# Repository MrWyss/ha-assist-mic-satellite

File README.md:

# Voice Assistant Mic Satellite

***<p align="center" style="text-align: center;">«The VA Mic Satellite is a compact, ESPHome-based microphone solution designed to integrate with your existing sound setup..»</p>***

## Changes

>📢 2025-11-23: Firmware release [v2.0.1](https://github.com/MrWyss/ha-assist-mic-satellite/releases/tag/v2.0.1) 
>
>Memory improvements: 
>
> - Allows to run 2 wake words simultaneously
> - ESPHome 2025.11.0
> 
>📢 2025-10-03: Firmware release [v2.0.0](https://github.com/MrWyss/ha-assist-mic-satellite/releases/tag/v2.0.0) 🎉🎉🎉: **Mayor Release**, this pushes the [M5Stack AtomS3](https://docs.m5stack.com/en/core/AtomS3) to **it's limit**. With these new features 
> - Option to change from "Okey Nabu" to "Hey Jarvis" and back
> - "Set Up Voice Assistant" wizard will run on first boot
> - ESPHome 2025.9.2
>
>... [Read more](https://github.com/MrWyss/ha-assist-mic-satellite/releases)
>
>📢 2024-08-19: Version 1 released. 🎉🎉🎉 and  [PCB rev. 3](https://github.com/MrWyss/ha-assist-mic-satellite/discussions/15#discussion-7049397) has arrived and tested successfully. 🥳. See the new firmware [in action](https://github.com/MrWyss/ha-assist-mic-satellite/discussions/16#discussioncomment-10387199) on a [mic stand](https://github.com/MrWyss/ha-assist-mic-satellite/discussions/16#discussioncomment-10387101) 😆.
>
>📢 2024-08-12: I just came across the [announcement](https://www.youtube.com/watch?v=Vp5q4RIwCX4) of **Satellite1** by [Future Proof Homes](https://futureproofhomes.net). It’s an amazing initiative! 😎 My project is entirely different and not comparable to theirs. The similar name is just a coincidence. Definitely check them out!

## Features

A ~~tiny~~ Atom version of the [ESP32-S3-BOX](https://esphome.io/projects/index.html)

- Local / On Device **wake word detection** (😲 holy cow, this works fast and so well)
- Redirect TTS to a configurable **media player entity** e.g. SONOS, to play the response
- HA **Assist Pipeline integration**
- Toggle **mute**, toggle **conversation text** and control display **brightness**
- **Show current state** (listening, idle, request, response) on the display. It is fairly readable, though it requires good eyesight 👀.
- **Timers** support (plural), realistically up to 4 timers
- Easy firmware flashing via the [web installer](https://mrwyss.github.io/ha-assist-mic-satellite/)
- Managed updates

### Roadmap

If anyone is interested in contributing, here are some ideas:

- [ ] Better alarm **sound files** [#10](https://github.com/MrWyss/ha-assist-mic-satellite/issues/10)
  
## TL;DR

Gather the following items: [M5Stack AtomS3](#bom), [pcb](#pcb), [pin headers and pin sockets](#bom) and an [INMP441](#bom) breakout board.
3D print the [case](#case), [assemble](#assembly) it, [flash the firmware](#firmware), [configure](#home-assistant) the device in Home Assistant.

## Try it out / Tricks

- **Wake Word**: "Okay Nabu" (or "Hey Jarvis")
- Create a timer, *Create a 3 minute timer for Bananas*, *Cancel Bananas timer*
- The display itself is also a button, so you can **long press (~800ms) to mute** the device, it stops listening for the wake word. Holding for ~10s factory resets the device.
- If you have [Music Assistant](https://music-assistant.io) you can change the **announcement volumes**. Goto the Music Assistant Addon -> Settings -> Players -> Your Speaker -> Configure -> Announcements configuration

## Hardware

### BOM

- [M5Stack AtomS3](https://docs.m5stack.com/en/core/AtomS3) ~15$
- [PCB](#pcb) ~5$ + shipping
- [Case](#case) ~0.5$ filament
- **INMP441** breakout board (usually comes with pin sockets) ~2$
  - 2x Pin socket 1x03 2.54mm (J3, J4)
- 1x Pin header 1x05 2.54mm (J1)
- 1x Pin header 1x04 2.54mm (J2)
- M2 x 5mm screw nylon or with metal with nylon washer (optional)

### PCB

The pcb was designed in KiCAD. [KiCAD Canvas Online View](https://kicanvas.org/?github=https%3A%2F%2Fgithub.com%2FMrWyss%2Fha-assist-mic-satellite%2Ftree%2Fmain%2Fpcb%2FMic%2520HAT%2520for%2520M5Stack%2520Atom) | [KiCad Project](pcb/Mic%20HAT%20for%20M5Stack%20Atom) | [PCB Step File](<pcb/Mic HAT for M5Stack Atom/Mic HAT for M5Stack Atom.step>)

Order from [PCBWay Project Link](https://www.pcbway.com/project/shareproject/HA_Assist_Mic_Satellite_f5cc4682.html) (🛒 affiliated link)

| PCB front | PCB back |
|:-------------------------:|:-------------------------:|
| | |

### Case

#### Hat

The case was designed in Fusion 360 and exported as 3mf files and step files. [Step files](case/step) | [3mf files](case/3mf)
It shouldn't need any supports for 3d printing, but I recommend printing it with your high detail settings. It is rather small.

- [Hat case body](case/3mf/MicHatCaseBody.3mf)
- [Hat case top](case/3mf/MicHatCaseTop.3mf)

#### Optional (boom, wind screen, stand)

[Boom for Grove connector](case/3mf/MicHatHolderGrove.3mf), the boom was designed for the Grove connector, as it is more centered. I sacrificed a sleeved USB cable and attached a Grove connector to it. It's supposed to be a press fit. [Mic wind screen](case/3mf/MicHatCaseWindShield.3mf), this is purely cosmetic and serves no functional purpose. [Mic stand](case/3mf/MicStandMicAll.3mf), to assemble the mic stand, you need a 8mm (~1 meter / hollow) aluminum rod. Cut into approximately three 10cm pieces, one 20cm (vertical) and one 25cm (horizontal).

### Assembly

Pretty straight forward. Solder the header sockets and pins to the pcb and to the INMP441.

>❗Check the direction of the header sockets and pins. Especially on the INMP441, the side with mic icon should face the same direction as the screen.

Put it in the case, screw it together and attach the HAT to the AtomS3.

## Software

- [Home Assistant](https://www.home-assistant.io) (*ESPHome not required only if you want to adopt the device*)
- [Music Assistant](https://music-assistant.io) (optional)
- A **media player entity** (e.g. media_player.office)

### Firmware

The firmware is available here: [Web Installer](https://mrwyss.github.io/ha-assist-mic-satellite/) or [ESPHome yaml](code/esphome/va-mic-sat-atoms3.yaml)

This has been frankensteined together from various sources. I will try to give [credit](#credits) where [credit](#credits) is due.

### Home Assistant

The device should get auto discovered.

We need to tick **Allow the device to perform Home Assistant actions**. Since the firmware will call the `media_player.play_media` service, we need to allow this.

While you here, click on **device** and change paste your media player entity id where the announcement should be played.

### Sounds

There are **two** sound files required. One for when the device is listening, this is the silent wav file, the second is for the alarm ringtone.

Currently the firmware is configured that the media player streams the files directly from github, in other words it (media_player) requires an internet connection. If you want to change this, adopt the device in ESPHome and change the following lines to something like this:

```yaml
substitutions:
  # ....
  timer_sound_file: media-source://media_source/local/my-alarm.mp3
  silence_sound_file: media-source://media_source/local/my-silence.mp3
```

To copy the sound files to for instance the home assistant, you can use the vscode addon or samba share. See more [Home Assistant Docs](https://www.home-assistant.io/integrations/media_source/)

## How it works

### Simplified Process

```mermaid
sequenceDiagram
    participant Mic Satellite
    participant Assist Pipeline
    participant media_player
    Mic Satellite->Mic Satellite: wake word detection
    Mic Satellite->>media_player: trigger action media_player.play_media (announcement / silent audio)
    media_player->media_player: lower volume
    Mic Satellite->Mic Satellite: listening  
    Mic Satellite->>Assist Pipeline: send intent audio
    Assist Pipeline->>Mic Satellite: response mp3_url
    Mic Satellite->>media_player: trigger action media_player.play_media (announcement / mp3_url)
    media_player->media_player: play response
```

### Wiring / Schematics

[KiCAD Schematic](<pcb/Mic HAT for M5Stack Atom/Mic HAT for M5Stack Atom.kicad_sch>) | [KiCAD Canvas Online View](https://kicanvas.org/?github=https%3A%2F%2Fgithub.com%2FMrWyss%2Fha-assist-mic-satellite%2Ftree%2Fmain%2Fpcb%2FMic%2520HAT%2520for%2520M5Stack%2520Atom)

All the the pcb hat does is connecting the INMP441 pins to the AtomS3 pins.

<details><summary>Pin mapping table</summary>

|AtomS3 Pin|INMP441 Pin|
|:----------:|:-----------:|
|3V3| VDD|
|GND | GND + L/R|
|G5 (GPIO5) | WS|
|G6 (GPIO6) | SCK|
|G7 (GPIO7) | SD|

</details>

Additionally, it exposes the remaining pins of the AtomS3 and adds two solder bridges (JP1 and JP2). G8, G38, and G39 are available to use for other purposes. So is the Grove connector (G1, G2). Power (+3V3 and +5V) and ground are also available.

The solder bridges are used to change the audio channel, left or right. There are two configurations:

- Left channel: JP1 bridged and JP2 not bridged (default)
- Right channel: JP1 not bridged and JP2 bridged

>❗To change the configuration, both solder bridges need to be modified. Cut one and bridge the other. I cloud otherwise short +3V3 to GND.

## Picture Gallery

<details><summary>Videos and Pictures</summary>

### Demo Video v1.0.0

https://github.com/user-attachments/assets/9a9f7f58-b787-4129-acef-4c1b4aa1fa7d

### Demo Pictures v1.0.0

### Close Ups

|Close up | Full device with cable&nbsp;&nbsp;&nbsp;&nbsp;&nbsp;&nbsp;&nbsp;&nbsp;&nbsp;&nbsp;&nbsp;&nbsp;&nbsp;&nbsp;&nbsp;&nbsp;&nbsp;&nbsp;&nbsp;&nbsp;&nbsp;&nbsp;&nbsp;&nbsp;&nbsp;&nbsp;&nbsp;&nbsp;&nbsp;&nbsp;&nbsp;&nbsp;&nbsp;&nbsp;&nbsp;&nbsp;&nbsp;&nbsp;&nbsp;&nbsp;&nbsp;&nbsp;&nbsp;&nbsp;&nbsp;&nbsp;&nbsp;&nbsp;&nbsp;&nbsp;&nbsp;&nbsp;&nbsp;&nbsp;&nbsp;&nbsp;|
|:-------------------------:|:-------------------------:|
| | |

### Archive

|Muted            |  Intent in Action|
|:-------------------------:|:-------------------------:|
| | |

</details>

## Background

I am not an electrical engineer nor a software developer. This project is for fun and to learn new things, such as PCB design with KiCad, CAD, and ready-made ESPHome projects.

I am aware that Nabu Casa is working on a [Voice Kit](https://github.com/esphome/voice-kit); in fact, many things are directly taken from their project.
I am excited to see what the final product will look like and might even buy it myself.

My motivation was to have a small device that integrates with my existing sound setup (SONOS, in my case) rather than having a separate speaker.

## License

I wasn't sure if I should use the same license as the ESPHome project, but I think it is fine.

## Contributing

**Please do**, create issues, pull requests, open a discussion or DM me here. I am happy to help and learn from you.

## Credits

- [HA Voice Kit](https://github.com/esphome/voice-kit)
- [ESPHome Voice Assistant Github Repo](https://github.com/esphome/firmware/tree/main/voice-assistant/)
- [Smart Home Circle](https://smarthomecircle.com/How-I-created-my-voice-assistant-with-on-device-wake-word-using-home-assistant)
- [Community](https://community.home-assistant.io/t/esphome-voice-assistant-speech-output-to-home-assistant-media-player/588337/18)
- And obviously the Nabu Casa team

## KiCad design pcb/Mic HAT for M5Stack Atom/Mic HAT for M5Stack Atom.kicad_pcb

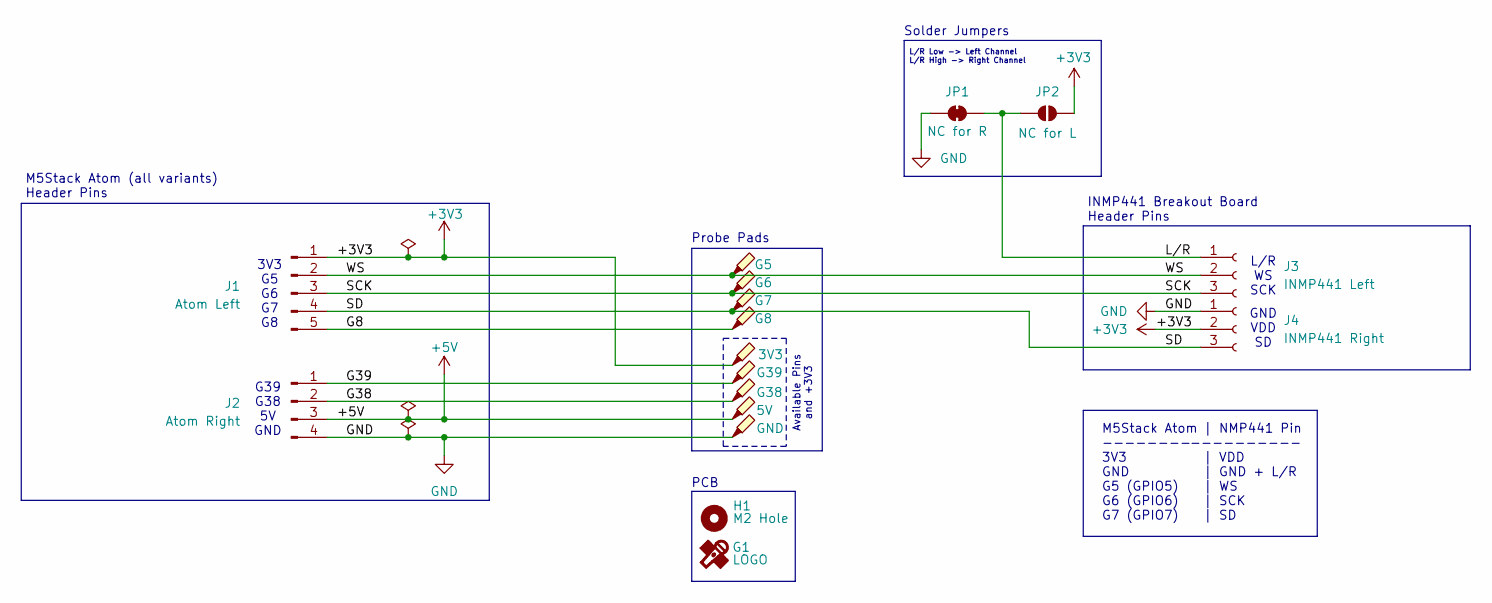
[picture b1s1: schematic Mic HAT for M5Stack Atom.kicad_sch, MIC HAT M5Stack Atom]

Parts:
3V3: 3V3; TestPoint_THTPad_D1.5mm_Drill0.7mm
5V1: 5V; TestPoint_THTPad_D1.5mm_Drill0.7mm
G1: LOGO; Logo
G5: G5; TestPoint_THTPad_D1.5mm_Drill0.7mm
G6: G6; TestPoint_THTPad_D1.5mm_Drill0.7mm
G7: G7; TestPoint_THTPad_D1.5mm_Drill0.7mm
G8: G8; TestPoint_THTPad_D1.5mm_Drill0.7mm
G38: G38; TestPoint_THTPad_D1.5mm_Drill0.7mm
G39: G39; TestPoint_THTPad_D1.5mm_Drill0.7mm
GND1: GND; TestPoint_THTPad_D1.5mm_Drill0.7mm
H1: M2 Hole; M2Hole
J1: Atom Left; PinHeader_1x05_P2.54mm_Vertical
J2: Atom Right; PinHeader_1x04_P2.54mm_Vertical
J3: INMP441 Left; PinSocket_1x03_P2.54mm_Vertical
J4: INMP441 Right; PinSocket_1x03_P2.54mm_Vertical
JP1: NC for R; SolderJumper-2_P1.3mm_Bridged_Pad1.0x1.5mm
JP2: NC for L; SolderJumper-2_P1.3mm_Open_Pad1.0x1.5mm

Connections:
+3V3: 3V3.1, J1.1, J4.2, JP2.1 (A)
+5V: 5V1.1, J2.3
/G8: G8.1, J1.5
/G38: G38.1, J2.2
/G39: G39.1, J2.1
/L/R: J3.1, JP1.1 (A), JP2.2 (B)
/SCK: G6.1, J1.3, J3.3
/SD: G7.1, J1.4, J4.3
/WS: G5.1, J1.2, J3.2
GND: GND1.1, J2.4, J4.1, JP1.2 (B)

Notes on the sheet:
3V3 G5 G6 G7 G8
M5Stack Atom (all variants) Header Pins
L/R WS SCK
Available Pins and +3V3
Solder Jumpers
M5Stack Atom -------- 3V3 GND G5 (GPIO5) G6 (GPIO6) G7 (GPIO7)
Probe Pads
PCB
| NMP441 Pin ---------- | VDD | GND + L/R | WS | SCK | SD
INMP441 Breakout Board Header Pins
GND VDD SD
G39 G38 5V GND
L/R Low -> Left Channel L/R High -> Right Channel

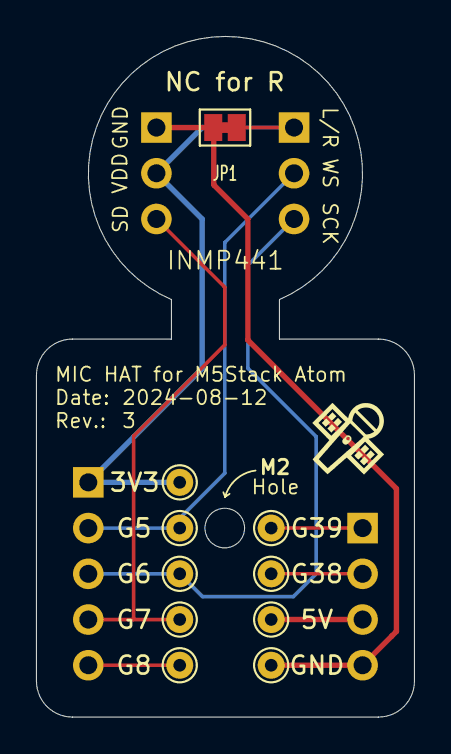
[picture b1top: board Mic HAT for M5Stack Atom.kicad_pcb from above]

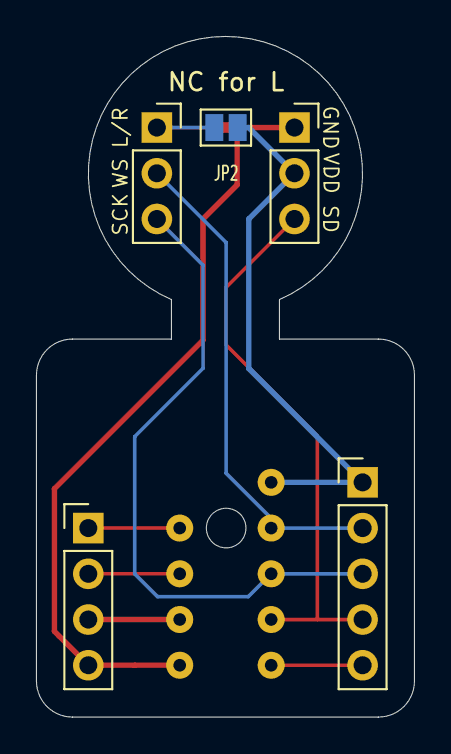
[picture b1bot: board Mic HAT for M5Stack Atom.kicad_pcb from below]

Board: 2 copper layers, 21.0 x 37.8 mm, 17 parts (5 on the bottom side), 10 nets.

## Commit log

2024-08-06 fix broken pcbway link
2024-08-06 3d case files and assembly instructions
2024-08-06 README.md cleanup
2024-08-06 fix links in README.md
2024-08-07 Clean up README.md and code folder structure
2024-08-08 first dev release of firmware
2024-08-08 online sound file and fix adopt url
2024-08-08 publish workflow test
2024-08-08 test workflow fixes
2024-08-08 updated workflows and create static folder
2024-08-08 esphome-project-template
2024-08-08 added description and the pull request workflow
2024-08-08 chore: Update publish workflow only to run when esphome configs have changed.
2024-08-08 fix index.md
2024-08-08 remove binary and trigger test the workflow
2024-08-08 fix sound link
2024-08-08 better README
2024-08-08 prep for Managed Updates
2024-08-08 test update
2024-08-08 adding diag buttons to check for updates
2024-08-08 fix compile error
2024-08-09 Create LICENSE
2024-08-09 fixes and add credits
2024-08-09 add esphome version for build
2024-08-09 trigger firmware build
2024-08-09 shields.io & tag line update
2024-08-09 pcb step file
2024-08-09 stl test
2024-08-09 STL Previews
2024-08-09 fix case text
2024-08-09 fix stl preview
2024-08-09 remove stl for pcb
2024-08-09 revert back, remove stl viewer seems to break the md
2024-08-10 Allow control of the display brightness Fixes #3
2024-08-10 human readable timer output and handling multiple timers
2024-08-10 basic timer display
2024-08-10 bit better font color and positioning
2024-08-10 only run when yaml has changed
2024-08-10 improved README
2024-08-10 nicer title
2024-08-11 spelling
2024-08-11 gallery clean up
2024-08-11 explain solder bridges and available pins
2024-08-11 Updates step files and adding grove handle
2024-08-11 improved mermaid simplified process
2024-08-11 replace esphome with firmware
2024-08-11 Added background and more on license and contributing
2024-08-11 better tag line
2024-08-11 link roadmap to
2024-08-11 fix issue link
2024-08-11 disable esp32_improv and therefore bluetooth
2024-08-11 timer tricks
2024-08-11 Update version shield
2024-08-11 Workflow for release to update manifest.json
2024-08-11 mostly comments removed
2024-08-11 status update
2024-08-11 include update in title picture
2024-08-11 adding release date shield
2024-08-11 updated roadmap
2024-08-11 some size tweaks on the title image
2024-08-12 rev. 3, fixed big oopsy reversed headers, aligned hole and some silkscreen alignments
2024-08-12 update pcb pictures and step files for rev 3
2024-08-12 Updated Case for rev 3
2024-08-12 status updates
2024-08-12 adding link to the fph announcement
2024-08-13 better fit for the holder
2024-08-13 added some pictures to the gallery
2024-08-13 gallery tweaks
2024-08-13 more tweaks to the gallery
2024-08-13 ignoring .vscode/settings.json
2024-08-13 spelling and consistency corrections
2024-08-14 Flickering slightly improved Fixes #17
2024-08-14 Improved click timing, hold is now mute, double and triple click available for other uses Fixes #19
2024-08-15 webinstaller: point to the latest version, project name consistency
2024-08-15 prepare for v0.0.2
2024-08-15 change update source url to the repo directly
2024-08-15 Reduced the delay to 2s (from 4s), keeps the playing media on low volume Fixes #10
2024-08-15 V0.0.2 (#21)
    * Display: Flickering slightly improved
    Fixes #17
    * Button: Improved click timing, hold is now mute, double and triple click available for other uses
    Fixes #19
    * Alarm: keeps the playing media on low volume when alarm is playing
    Fixes #10
2024-08-15 test combined workflow
2024-08-15 try with list
2024-08-15 try with released
2024-08-15 change to only edited
2024-08-15 back to published
2024-08-15 .disable seem not disabling the workflow
2024-08-15 test manual trigger
2024-08-15 release, edited or manual
2024-08-15 fix deprecated syntax and only on published
2024-08-15 fix version
2024-08-15 make it reusable
2024-08-15 calling workflows
2024-08-15 rename on dispatch
2024-08-15 on publish test
2024-08-15 maybe it need to run an os
2024-08-15 only on published?
2024-08-15 i guess tag needs to be removed too
2024-08-16 clean up workflows and combine them
2024-08-18 Redesign animations and text to optimize for the small screen Fixes #9
2024-08-18 prepare v1.0.0
2024-08-18 Changed to absolute paths
2024-08-18 fix folder spelling
2024-08-18 media files prep for v1.0.0
2024-08-19 better mute indication
2024-08-19 update mute screen, better mute indication
2024-08-19 better listening picture
2024-08-19 Announcement v1.0.0 and demo pics and video
2024-08-19 Redesign animations and text to optimize for the small screen (#22)
    * Redesign animations and text to optimize for the small screen
    Fixes #9
    * New screens with better readability
2024-08-19 Redesign animations and text to optimize for the small screen (#22) (#23)
    * Redesign animations and text to optimize for the small screen (#22)
    * Redesign animations and text to optimize for the small screen
    Fixes #9
    * New screens with better readability
2024-08-19 try new workflow from esphome
2024-08-19 disable on push to main
2024-08-19 new CI workflow
2024-08-19 combine name firmware?
2024-08-19 update static
2024-08-19 fixes ota update via gh-pages
2024-08-19 fixed shields and announcements
2024-08-19 added discussion links for the pcb and demo
2024-08-19 Update webinstaller links to generic url
2024-08-20 some touch-ups
2024-08-20 optional 3d files
2024-08-20 better mic stand instructions
2024-08-20 remove old workflow
2024-08-20 cosmetics
2024-08-20 upload the mic icon for future use
2024-08-20 laying egg
2024-08-21 adding status page summoned by double click
2024-08-21 better font, with AA, and refactored code
2024-08-21 better font
2024-08-21 better init phase
2024-08-21 prepare v1.1.0
2024-08-21 Tidy things up
2024-08-21 center status page a bit
2024-08-21 working multiline, sort of, still needs tweaking.
2024-08-21 fix 31 character truncation, display time 8 sec as global var
2024-08-21 adding quotes to the allowed list
2024-08-21 refactor switch statement
2024-08-21 added todo and set use_wake_word: false
2024-08-21 font anti-aliasing set to 4
2024-08-22 added feets for the micstand
2024-08-22 Resolve issue where mute setting is not retained upon device reconnection to Home Assistant Fixes #24
2024-08-22 Updated middle section of the mic stand
2024-08-22 better instructions for mic stand
2024-08-22 Update road map
2024-08-24 updated esphome to 2024.8.0
2024-08-24 Release announcement and additional 3d print files for the mic stand
2024-08-24 forgot to add Multi-line support
2024-08-24 announcement
2024-08-25 replaced repeat with wait_until
2024-08-25 contributors/credits page
2024-08-25 Fix wake word restart when voice assist response ended Fixes #30
2024-08-25 prepare v1.1.1
2024-08-25 force ci workflow to run again
2024-08-25 don't use factory images
2024-08-25 force another ci workflow run
2024-08-25 Release announcement v1.1.1
2024-10-18 Change mute screen to be visible from further away Fixes #33
2024-10-18 bump version to 1.1.2
2024-10-18 bump esphome version to 2024.10.0
2024-10-27 An announcement is already in progress.... Fixes #35
2024-10-27 Bump esphome version to 2024.10.2
2024-10-27 Bump version to v1.1.3
2024-11-21 Fix Font glyphsets for ESPHome version 2024.11 Fixes #37
2024-11-21 Bump version to v1.1.4
2024-11-21 Update ESPHome version to 2024.11.0 in publish workflow
2024-11-21 Update README.md for firmware release v1.1.4 and improve media player entity description
2024-12-19 Shorten Device Friendly Name Fixes #38
2024-12-19 Update ESPHome version to 2024.12.1 in publish workflow
2024-12-19 Bump version to v1.1.5
2024-12-19 Added v1.1.5 announcement
2024-12-22 Polish project name and device name Fixes #41
2024-12-22 Bump version to v1.1.6
2024-12-22 Adopt voice assistant sounds Fixes #42
2024-12-22 Announcements for v1.1.6
2025-10-03 Fixes #46 and #7
2025-10-03 Update ESPHome version to 2025.9.2 in publish workflow
2025-11-23 Reduce font bits per pixel from 4 to 2 for improved memory efficiency
2025-11-23 Update firmware to v2.0.1 with memory improvements
